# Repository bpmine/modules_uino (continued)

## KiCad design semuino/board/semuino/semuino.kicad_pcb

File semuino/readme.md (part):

# SEMUINO - ECLAIRAGE ARMOIRE A SEMIS

Toutes les plantes ont besoin de lumière.

Les semis ont aussi besoin de lumière.

Pour une croissance optimale, il faut éclairer les semis pendant une certaine durée journalière et avec un spectre de lumière donné (couleurs).

C'est ce que réalise le meuble à semis sur la photo suivante.

## Description de l'éclairage souhaité

Pendant la phase de germinaison et de croissance, il est conseillé d'éclairer avec une teinte composée de 20% de bleu et 80% de rouge.
La lumière doit être répartie de façon homogène pour éviter que les pousses prenent une direction particulière ou/et ne mollissent.

Nous avons choisi une durée d'éclairage de 16 heures par jour.

Pour se rapprocher du cycle naturel, il y'a une montée de la luminosité pendant les 2 premières heures et une descente les 2 dernières heures de la journée.

Pendant la deuxième phase de croissance, la lumière est blanche. Mais les avis divergent. Le meuble permet donc de choisir plusieurs modes d'éclairage.

## Description du meuble

### Composition du meuble

Il est issu de la récupération d'un vieux meuble cassé et dont nous n'avions plus l'usage. 

Le tiroir du bas est utilisé pour mettre des semis.

Le tiroir du milieu est retourné et servira de plafond au premier étage (en bas).

Au dessus du tiroir du milieu pourront être posé des petits plants de plus grande taille. Un tiroir peut également être inséré au dessus pour permettre de poser d'autres semis.

Des bandeaux de LEDs sont collés au dessus et dans le tiroir du milieu. Ils éclairent de façon homogène les semis des deux étages intérieurs.

Il est prévu d'ajouter un étage au dessus du meuble toujours sur le même principe.

### Mode d'emploi

#### Panneau de commande

Le bouton d'alimentation générale 12V permet d'allumer ou d'éteindre le boîtier. Une LED rouge s'allume lorsque celui-ci est en position "marche".

Le bouton d'alimentation auxiliaire 5V permet d'alimenter les LEDs RGB. Une LED bleue s'allume lorsqu'il est dans la position "marche".

Un bouton de sélection permet de modifier le mode de fonctionnement du meuble. Une LED verte permet d'indiquer à l'utilisateur l'état de fonctionnement du meuble.

#### Principe de fonctionnement du sélecteur

Le meuble a trois modes de fonctionnement que l'on peut sélectionner successivement à l'aide du bouton de sélection.

Mode | Nom | Description
--- | --- | ---
0 | OFF | Toutes les LEDs sont éteintes
1 | Auto/Horloge | Les LEDs s'allument entre 6h et 22h selon un mode d'éclairage défini
2 | ON | Les LEDs s'allument

Le mode choisi est sauvegardé dans le boîtier. Lorsqu'on l'éteint et qu'on le rallume, le réglage est retrouvé.

Lorsqu'on change de mode, la LED verte s'allume une première fois puis clignote rapidement autant de fois que le numéro du mode choisi.

La façon dont s'allume les LEDs (étages allumés) est configurable. Ce réglage est aussi mémorisé par le boîtier.

#### Mode de configuration

Pour entrer dans le mode de configuration, il faut appuyer sur le bouton de sélection pendant plus de 4 secondes. 
La LED verte clignote plusieurs fois très rapidement pour indiquer l'entrée dans le menu.
Elle reste ensuite allumée pour indiquer que l'on est dans le mode de configuration

En appuyant sur le bouton de sélection, on peut faire défiler les différents modes d'éclairage. Les LEDs du meuble s'allument en conséquence.
Lorsque le mode d'éclairage souhaité est rencontré, il faut presser pendant environ 4s sur le bouton de sélection jusqu'à ce que la LED verte s'éteigne.

La LED verte clignote ensuite pour rappeller le mode de fonctionnement en cours (voir partie précédente).

#### Récaputulatif de l'état de la LED verte

Etat | Description
Clignote très rapidement au démarrage | Impossible de lire la date et l'heure: Vérifier la pile 3V à l'intérieur. Le meuble est bloqué.
S'allume une fois puis cliqnote n fois rapidement au démarrage | Indique/rapelle le mode de fonctionnement (autant de foir que le numéro de mode)
Eteinte | fonctionnement normal
Cliqnote n fois rapidement après une action | Indique/rapelle le mode de fonctionnement (autant de fois que le numéro de mode)
Clignote toutes les 2s | La terre est sèche: Il faut probablement arroser
Clignote très très rapidement pusieurs fois puis reste allumée | Entrée en mode de configuration de l'éclairage
Allumée fixe | Mode de configuration en cours

#### Usage du bouton de sélection

Action | Description
--- | ---
Appui court | Changer le mode de fonctionnement (OFF / Auto-Horloge / ON)
Appui long | Entrer en mode de configuration

##### En mode configuration

Action | Description
--- | ---
Appui court | Changer le mode d'éclairage des LEDs du meuble
Appui long | Quitter le mode de configuration (et sauver le réglage)
 
#### Description du mode auto

En mode auto, le semuino gère l'éclairage tout seul de la façon suivante:

- De 6h à 7h, la lumière blanche monte toute seule
- de 7h à 12h, la lumière est de type horticole (LEDs RGB et LEDs 12V majoritairement en rouge spécial)
- de 12h à 14h, la lumière est au maxium (LEDs RGB blanches)
- de 14h à 21h, on revient à l'éclairage horticole normal
- de 21h à 22h, la lumière blanche descend toute seule

## Détail technique

### Schéma et conception

[Schéma et PCB de la carte](board/semuino)

Le carte semuino est architecturée autour d'un arduino nano dans sa configuration réduite "standalone".

Elle comporte les éléments suivants:

- Module Nano;
- module RTC;
- module DHT22 pour mesurer l'humidité et la température ambiante;
- trois Sorties de puissance 12V pour alimenter des LEDs horticoles en mode ON/OFF;
- une alimentation 5V pilotable pour alimenter les bandeaux de LEDs LEDs RGB;
- trois sorties pour bandeaux de LEDs RGB;
- trois entrées pour mesure d'humidité du sol;
- un bouton de sélection de mode;
- une entrée/sortie disponible.

Dans cette configuration, le semuino fonctionne de manière autonome. Il se base sur la date et l'heure pour appliquer l'éclairage souhaité.
Il est également possible de prendre en compte la température et l'humidité (en fonction du programme présent dans le nano).
L'utilisateur peut changer le mode à l'aide d'un bouton de sélection.

La version plus élaborée de la carte semuino comporte en plus un ESP01 et une extension pour connecter un petit écran OLED (type SSD1306 128x64).

Dans cette version, l'arduino Nano devient un simple esclave I²C parmi les autres (RTC et écran). C'est le module ESP01 qui gère tout.
Ce dernier peut aussi fonctionner de façon autonome comme pour la configuration précédente.
Mais il peut communiquer en Wifi et disposer de plus de mémoire pour réaliser plus de choses.

L'ensemble logique de la carte est alimenté en 3.3V (Nano, RTC, ESP01, DHT22, ...). Pour le Nano, il est nécessaire d'ajouter une diode pour permettre l'utilisation simultanée de l'alimentation principale avec celle de l'USB.
Le 3.3V de la carte est appliqué à l'entrée d'alimentation 5V du nano. En effet, la broche 3.3V du Nano est une sortie reliée au régulateur intégré de la puce USB. Elle ne sera pas utilisée.

Tous les composants autour du Nano sont alimentés en 3.3V et sont compatibles avec ce niveau de tension. Le fait que le Nano soit alimenté en ~2.6 peut poser un problème de pilotage du signal de data des LEDs RGB pour lesquels la tension requise pour un niveau haut
est de 0.7 Vcc soit 3.5V. En cas de problème, on peut ajouter "en volant" un adaptateur de niveau 3.3V vers 5V qui fera la conversion. Les premiers essais ont validé le schéma initial.

**Attention:** Selon l'alimentation externe utilisée pour obtenir le 5V, il peut être nécessaire d'ajouter un condensateur de filtrage sur le POWER_5V. Cela a été le cas sur notre prototype. Sans ce condensateur, l'alimentation 5V n'était pas correctement filtrée et le bandeau RGB ne fonctionnait pas. 
Au mieux il clignotait, au pire il affichait des couleurs aléatoires.

### Composants

#### Externes

Nom | Description
--- | --- 
WS2812B 5m 300 LEDs | Bandeau RGB avec 300 LEDs / 5M / 18W
 ? | Capteur d'humidité capatitif
SSD1306 | Ecran OLEB 128x64

#### Sur la carte (principaux)

Nom | Description
--- | --- 
DHT22 | Capteur de température et d'humidité ambiante
Nano | Module Arduino Nano
ESP01 | Module ESP01 (pour connectivité wifi et pilotage de LCD)
RTC | Module RTC avec pile 3V
... | ...

A compléter...

### Les logiciels

Il y'a plusieurs types de logiciels différents pour l'arduino Nano:

Nom | Description | Lien
--- | --- | ---
semuino_test|Pour tester la carte semuino | 
semuino|Le programme standalone standard pour le Nano |
semuino_nano_slave|Le programme esclave I²C pour le nano |
semuino_nano_master_test|Un programme de test pour remplacer un maître I²C avec un Nano |

Le Nano est quasiment plein niveau RAM. Il n'est pas possible de gérer les trois RGB en même temps. Le RGB3 a pour l'instant été retiré.
Au niveau temps de cycle, il n'est pas possible d'utiliser le DHT22 en même temps que le bus I²C.

Pour l'ESP01, il n'y a qu'un seul programme:
Nom | Description | Lien
--- | --- | ---
semuino_esp01_master|Programme SEMUINO complet pour ESP01 | 

## Protocole d'échange I²C (Esclave Nano)

L'I²C permet à l'ESP01 d'accéder à l'écran, au RTC et au Nano. Cette partie décrit la gestion de l'esclave par le programme du Nano.

### Description des échanges I²C

Adresse de l'esclave: 0xA

Pour écrire une valeur, on envoie le numéro de registre (1 octet) puis la donnée à écrire.

Registre | Nom | R/W  | Taille | Description
--- | --- | --- | --- | ---
1 | Commandes | Ecriture | 1 octet | Contient les commandes pour agir sur les bandeaux de LEDs
2 | Level | Ecriture | 1 octet | Défini le niveau d'éclairage des LEDs RGB (entre 1 et 255)
3 | Modes RGB A | Ecriture | 1 octet | Contient les modes des bandeaux RGB 1 (4 bits de poids faible) et RGB 2 (4 bits de poids fort)
4 | Modes RGB B | Ecriture | 1 octet | Les 4 bits de poids faible correspondent au mode du bandeau RGB 3
5 | WRITE EEPROM | Ecriture | 2 octets | Le premier octet contient l'adresse EEPROM où écrire et le second contient la donnée à écrire
6 | Voyants | Ecriture | 1 octet | Etat des voyants (bit 0: LED verte)

Pour lire une valeur, on envoie le numéro de registre (1 octet) puis on demande la lecture des données.

Registre | Nom | R/W  | Taille | Description
--- | --- | --- | --- | ---
10 | Inputs | Lecture | 1 octet | Retourne l'état des entrées (bit 0: bouton de select)
11 | TEMP | Lecture | 1 octet | Retourne la température ambiante (en °C)
12 | HUM | Lecture | 1 octet | Retourne le taux d'humidité ambiante (en %)
13 | H1 | Lecture | 1 octet | Retourne la valeur du capteur d'humidité du sol n° 1 (0..255)
14 | H2 | Lecture | 1 octet | Retourne la valeur du capteur d'humidité du sol n° 2 (0..255)
15 | H3 | Lecture | 1 octet | Retourne la valeur du capteur d'humidité du sol n° 3 (0..255)
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
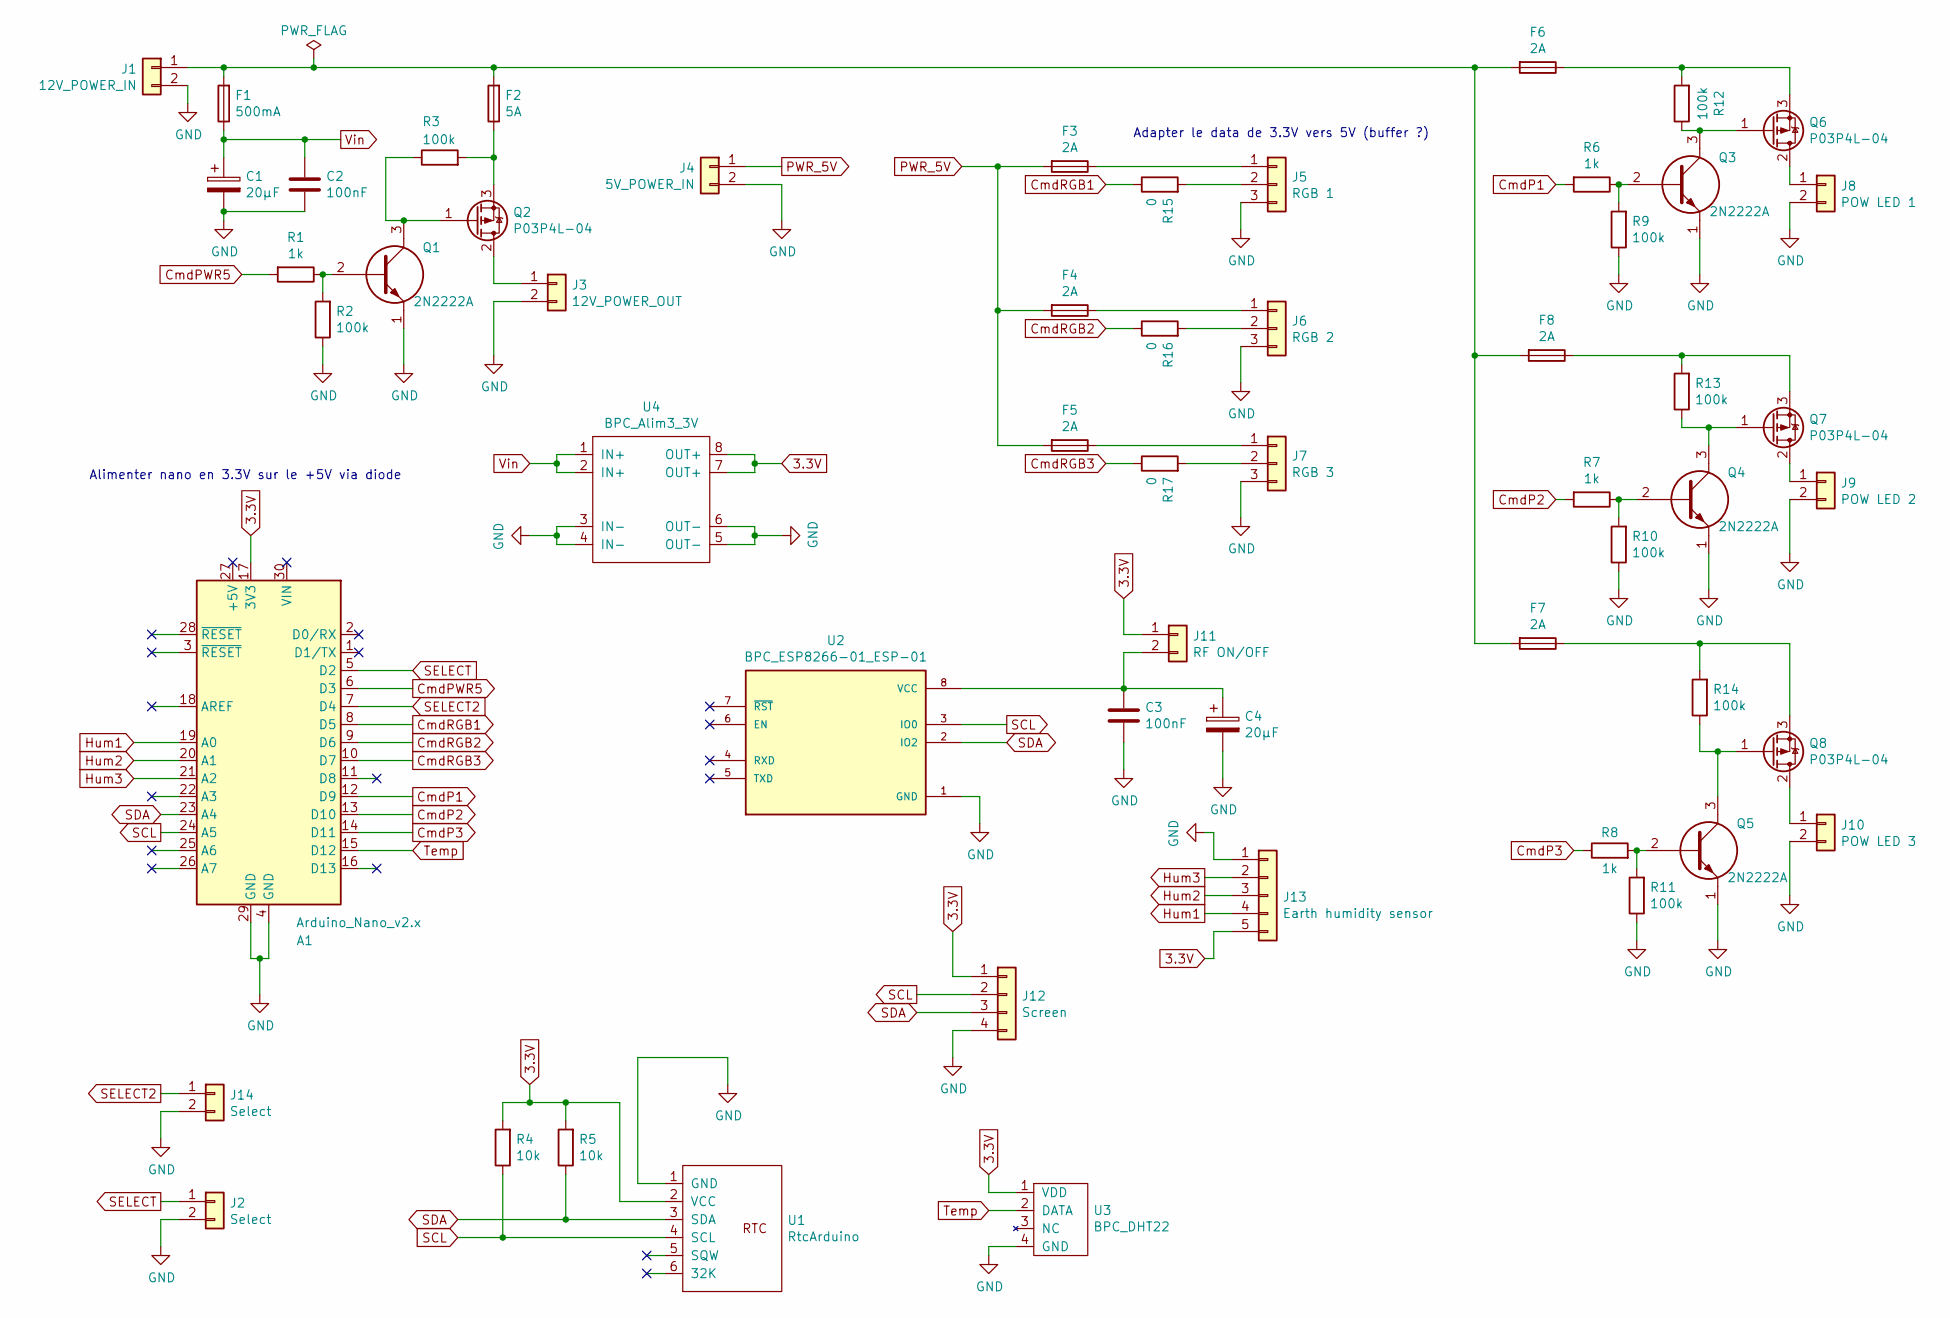
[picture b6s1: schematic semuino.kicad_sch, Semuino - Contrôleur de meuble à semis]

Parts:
A1: Arduino_Nano_v2.x; BPC_Arduino_Nano
C1, C4: 20µF; CP_Radial_D8.0mm_P3.80mm
C2, C3: 100nF; C_Disc_D7.0mm_W2.5mm_P5.00mm
F1: 500mA; Fuseholder_TR5_Littelfuse_No560_No460
F2: 5A; Fuseholder_Clip-5x20mm_Littelfuse_520_Inline_P20.50x5.80mm_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
F3, F4, F5, F6, F7, F8: 2A; Fuseholder_TR5_Littelfuse_No560_No460
J1: 12V_POWER_IN; TerminalBlock_Phoenix_MKDS-1,5-2_1x02_P5.00mm_Horizontal
J2, J14: Select; PinHeader_1x02_P2.54mm_Vertical
J3: 12V_POWER_OUT; TerminalBlock_Phoenix_MKDS-1,5-2_1x02_P5.00mm_Horizontal
J4: 5V_POWER_IN; TerminalBlock_Phoenix_MPT-0,5-2-2.54_1x02_P2.54mm_Horizontal
J5: RGB 1; TerminalBlock_Phoenix_MPT-0,5-3-2.54_1x03_P2.54mm_Horizontal
J6: RGB 2; TerminalBlock_Phoenix_MPT-0,5-3-2.54_1x03_P2.54mm_Horizontal
J7: RGB 3; TerminalBlock_Phoenix_MPT-0,5-3-2.54_1x03_P2.54mm_Horizontal
J8: POW LED 1; TerminalBlock_Phoenix_MKDS-1,5-2_1x02_P5.00mm_Horizontal
J9: POW LED 2; TerminalBlock_Phoenix_MKDS-1,5-2_1x02_P5.00mm_Horizontal
J10: POW LED 3; TerminalBlock_Phoenix_MKDS-1,5-2_1x02_P5.00mm_Horizontal
J11: RF ON/OFF; PinHeader_1x02_P2.54mm_Vertical
J12: Screen; JST_XH_B4B-XH-A_1x04_P2.50mm_Vertical
J13: Earth humidity sensor; TerminalBlock_Phoenix_MPT-0,5-5-2.54_1x05_P2.54mm_Horizontal
Q1, Q3, Q4, Q5: 2N2222A; TO-92; Manufacturer_Part_Number 2N2222A; Mouser Part Number 494-2N2222A
Q2, Q6, Q7, Q8: P03P4L-04; TO-220-3_Vertical
R1, R6, R7, R8: 1k; R_Axial_DIN0309_L9.0mm_D3.2mm_P2.54mm_Vertical
R2, R3, R9, R10, R11, R12, R13, R14: 100k; R_Axial_DIN0309_L9.0mm_D3.2mm_P2.54mm_Vertical
R4, R5: 10k; R_Axial_DIN0309_L9.0mm_D3.2mm_P12.70mm_Horizontal
R15, R16, R17: 0; R_Axial_DIN0309_L9.0mm_D3.2mm_P2.54mm_Vertical
U1: RtcArduino; BPC_RtcArduino
U2: BPC_ESP8266-01_ESP-01; BPC_XCVR_ESP8266-01_ESP-01; PARTREV V1.2
U3: BPC_DHT22
U4: BPC_Alim3_3V

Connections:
3.3V: A1.17 (3V3), J11.1, J12.1, J13.5, R4.2, R5.2, U1.2 (VCC), U3.1 (VDD), U4.7 (OUT+), U4.8 (OUT+)
CmdP1: A1.12 (D9), R6.2
CmdP2: A1.13 (D10), R7.2
CmdP3: A1.14 (D11), R8.1
CmdPWR5: A1.6 (D3), R1.2
CmdRGB1: A1.8 (D5), R15.1
CmdRGB2: A1.9 (D6), R16.1
CmdRGB3: A1.10 (D7), R17.1
GND: A1.4 (GND), A1.29 (GND), C1.2, C2.2, C3.2, C4.2, J1.2, J2.2, J3.2, J4.2, J5.3, J6.3, J7.3, J8.2, J9.2, J10.2, J12.4, J13.1, J14.2, Q1.1, Q3.1, Q4.1, Q5.1, R2.1, R9.1, R10.1, R11.1, U1.1 (GND), U2.1 (GND), U3.4 (GND), U4.3 (IN-), U4.4 (IN-), U4.5 (OUT-), U4.6 (OUT-)
Hum1: A1.19 (A0), J13.4
Hum2: A1.20 (A1), J13.3
Hum3: A1.21 (A2), J13.2
unnamed: F1.2, F2.2, F6.2, F7.2, F8.2, J1.1
unnamed: J3.1, Q2.2 (D)
unnamed: F3.1, J5.1
unnamed: J5.2, R15.2
unnamed: F4.1, J6.1
unnamed: J6.2, R16.2
unnamed: F5.1, J7.1
unnamed: J7.2, R17.2
unnamed: J8.1, Q6.2 (D)
unnamed: J9.1, Q7.2 (D)
unnamed: J10.1, Q8.2 (D)
unnamed: C3.1, C4.1, J11.2, U2.8 (VCC)
unnamed: Q1.2, R1.1, R2.2
unnamed: Q1.3, Q2.1 (G), R3.1
unnamed: F2.1, Q2.3 (S), R3.2
unnamed: Q3.2, R6.1, R9.2
unnamed: Q4.2, R7.1, R10.2
unnamed: Q5.2, R8.2, R11.2
unnamed: Q3.3, Q6.1 (G), R12.1
unnamed: F6.1, Q6.3 (S), R12.2
unnamed: Q4.3, Q7.1 (G), R13.1
unnamed: F8.1, Q7.3 (S), R13.2
unnamed: Q5.3, Q8.1 (G), R14.1
unnamed: F7.1, Q8.3 (S), R14.2
PWR_5V: F3.2, F4.2, F5.2, J4.1
SCL: A1.24 (A5), J12.2, R4.1, U1.4 (SCL), U2.3 (IO0)
SDA: A1.23 (A4), J12.3, R5.1, U1.3 (SDA), U2.2 (IO2)
SELECT: A1.5 (D2), J2.1
SELECT2: A1.7 (D4), J14.1
Temp: A1.15 (D12), U3.2 (DATA)
Vin: C1.1, C2.1, F1.1, U4.1 (IN+), U4.2 (IN+)

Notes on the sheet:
Alimenter nano en 3.3V sur le +5V via diode
Adapter le data de 3.3V vers 5V (buffer ?)

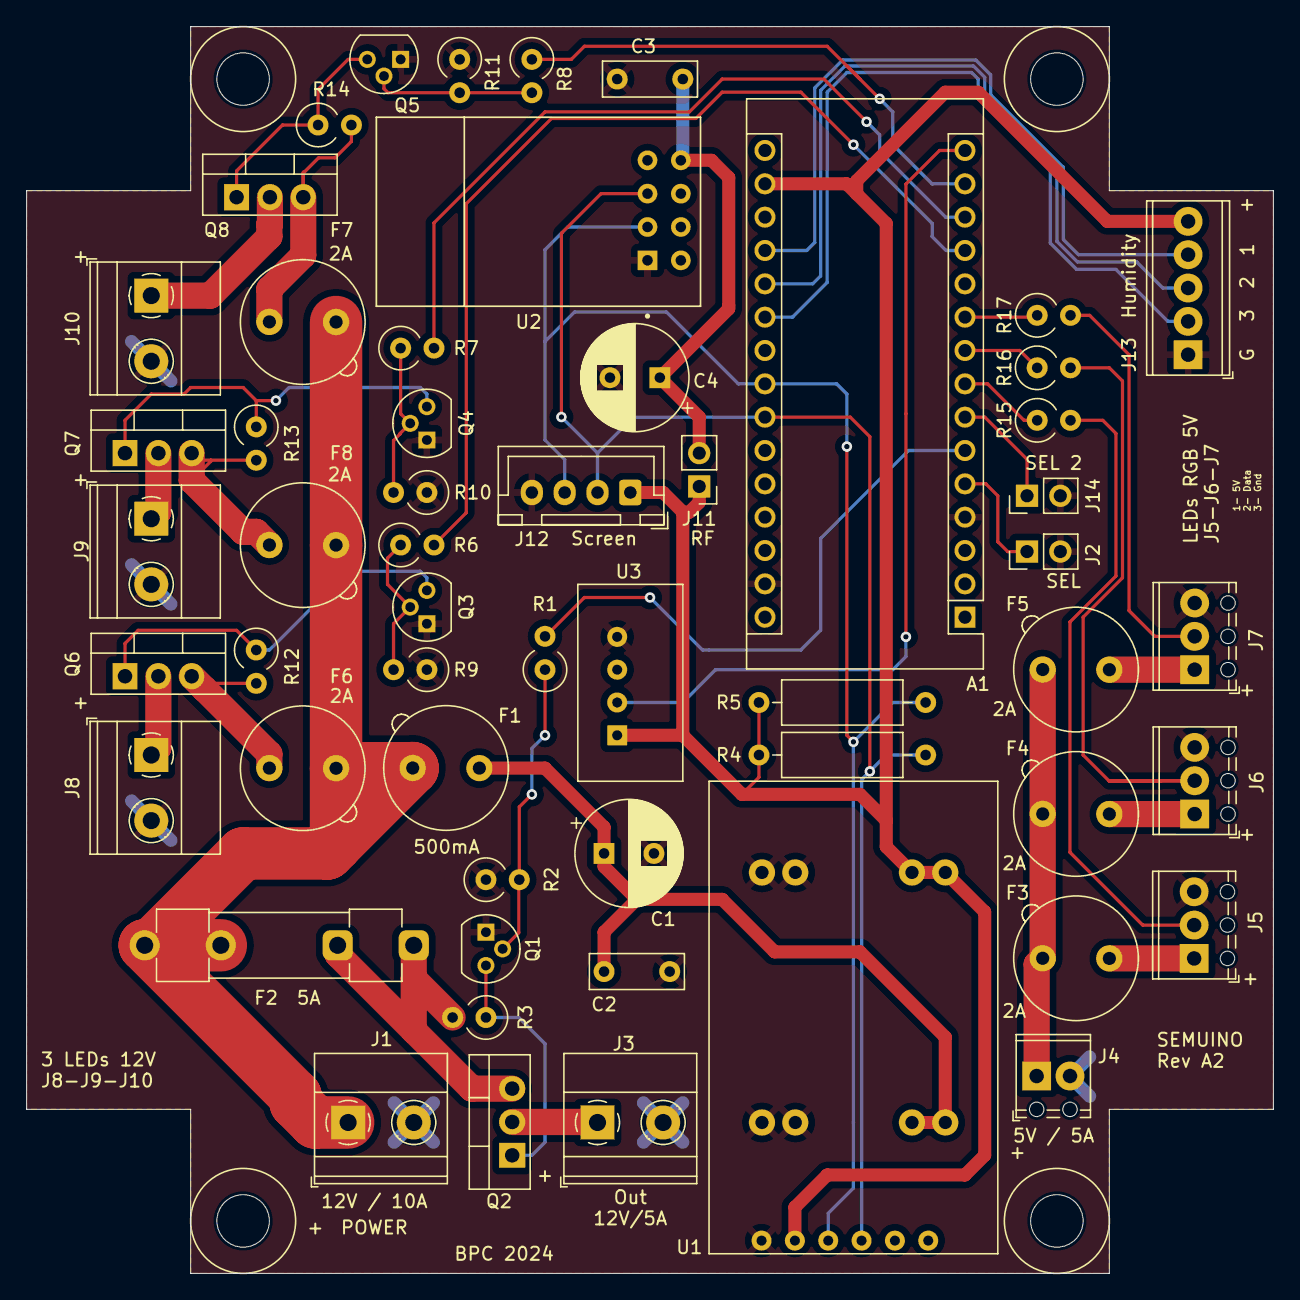
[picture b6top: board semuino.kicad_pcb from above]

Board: 2 copper layers, 95.0 x 95.0 mm, 56 parts (1 on the bottom side), 43 nets.

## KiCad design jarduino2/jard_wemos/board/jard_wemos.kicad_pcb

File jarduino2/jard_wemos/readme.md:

# Modules de commande des pompes en Wifi (jard_wemos)

Cette partie comporte la description de modules Wifi permettant de commander les pompes de transfert entre cuves.

Plusieurs cuves contiennent de l'eau de récupération des pluies.

Les cuves principales sont toujours en exédant d'eau, alors que les cuves proches des coins jardin sont en déficit d'eau.

Le rôle de ce système est de permettre un transfert d'eau automatique ou piloté à distance.

## Schéma d'ensemble des cuves

## Architecture du système

## Description des composants du système
### Module de pompage

Le module de pompage comporte:
- 1 alimentation 12V;
- 1 sortie pompe de 12V/5A;
- 3 entrées de type interrupteur (actif à l'état bas) pour la détection du niveau de cuve.

### Module d'affichage

Le module d'affichage comporte un écran, OLED.

Il permet de visualiser l'état des cuves et l'activité de pompage en temps réel.

### Serveur de contrôle

Le serveur comporte un broker MQTT pour centraliser les connexions des différents modules du système.

Un serveur reddis stocke tous les états, les réglages et les commandes des différentes applications.

Les applications sont les suivantes:
- Interraction avec les modules de pompage
- Publication des états sur les écrans
- Webservice pour exposer les services à des clients
- Automatisme de contrôle
- Logger

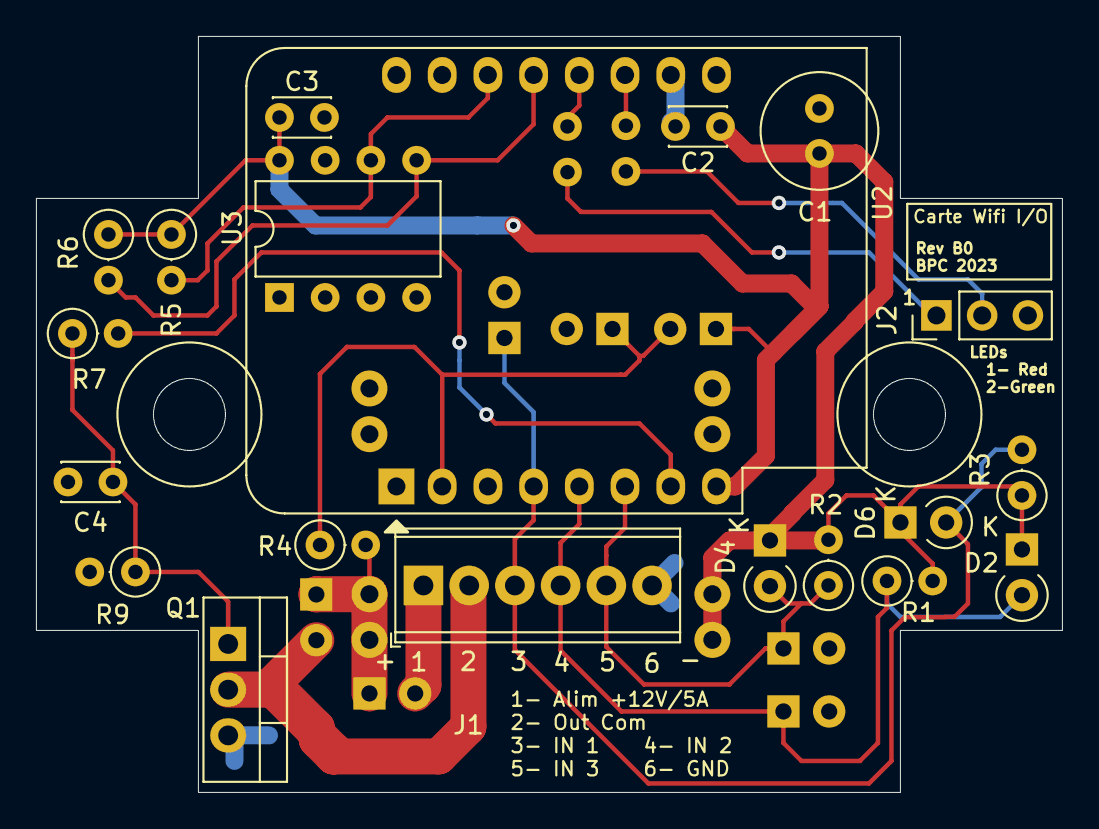
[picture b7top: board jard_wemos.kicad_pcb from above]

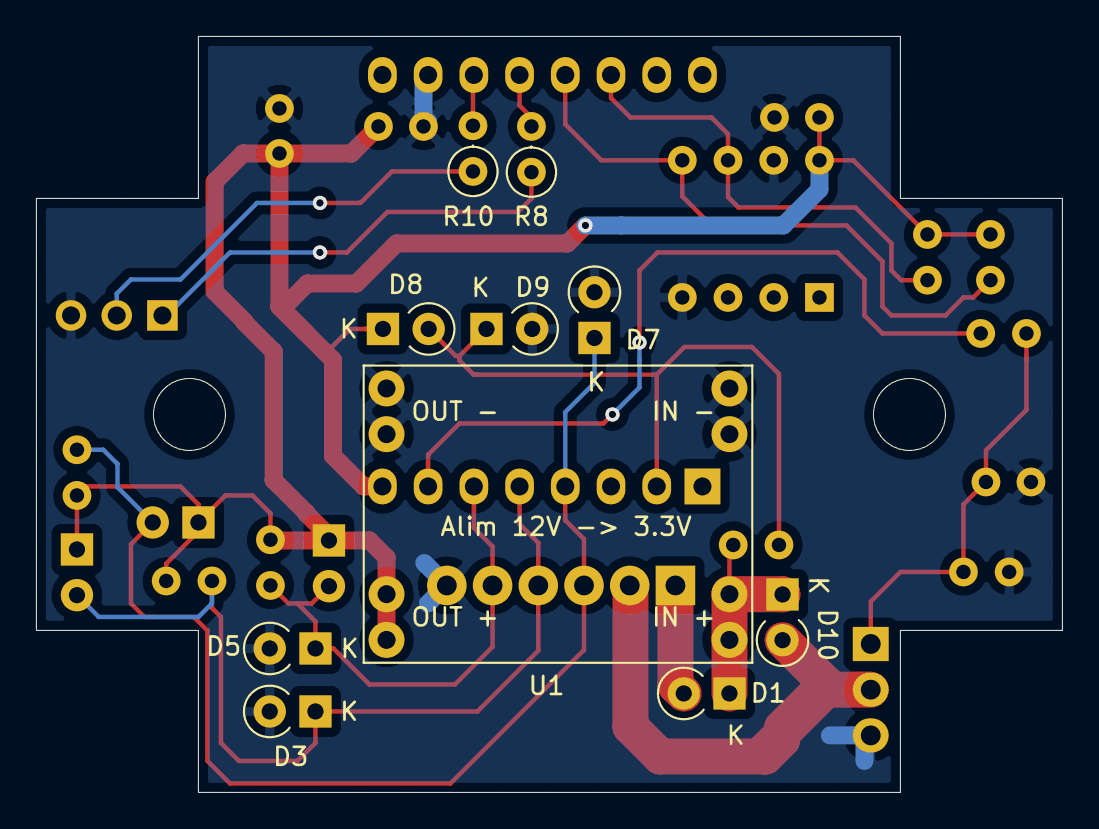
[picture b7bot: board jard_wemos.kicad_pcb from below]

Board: 2 copper layers, 57.0 x 42.0 mm, 30 parts (10 on the bottom side), 17 nets.

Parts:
C1: 20µF; C_Radial_D6.3mm_H7.0mm_P2.50mm
C2, C3, C4: 100n; C_Disc_D3.0mm_W2.0mm_P2.50mm
D1, D2, D3, D4, D5, D6, D7, D8, D9, D10: D; D_A-405_P2.54mm_Vertical_KathodeUp
J1: Conn_01x05; TerminalBlock_Phoenix_MPT-0,5-6-2.54_1x06_P2.54mm_Horizontal
J2: LEDs; PinHeader_1x03_P2.54mm_Vertical
Q1: BPC_IPP034N03L; TO-220-3_Vertical
R1, R2, R3, R9: 100k; R_Axial_DIN0207_L6.3mm_D2.5mm_P2.54mm_Vertical
R4: 1,2M; R_Axial_DIN0207_L6.3mm_D2.5mm_P2.54mm_Vertical
R5, R6: 10k; R_Axial_DIN0207_L6.3mm_D2.5mm_P2.54mm_Vertical
R7: 50; R_Axial_DIN0207_L6.3mm_D2.5mm_P2.54mm_Vertical
R8, R10: 100; R_Axial_DIN0207_L6.3mm_D2.5mm_P2.54mm_Vertical
U1: BPC_Alim3_3V
U2: WeMos_D1_mini; WEMOS_D1_mini_light
U3: 24LC01; DIP-8_W7.62mm

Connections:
+3V3: C1.1, C2.1, C3.2, D2.1, D4.1, D6.1, D8.1, R1.2, R2.2, R3.1, R5.1, R6.1, U1.7, U1.8, U2.8, U3.8
+12V: D1.1, D10.1, R4.2, U1.1, U1.2
CMD_OUT_12V: R7.2, U2.7
GND: C1.2, C2.2, C3.1, C4.2, D3.2, D5.2, D7.2, D9.2, J1.6, J2.3, Q1.3, R9.2, U1.3, U1.4, U1.5, U1.6, U2.10, U3.4, U3.7
IN_1: D6.2, D7.1, J1.3, R3.2, U2.4
IN_2: D2.2, D3.1, J1.4, R1.1, U2.5
IN_3: D4.2, D5.1, J1.5, R2.1, U2.6
LED_ROUGE: R8.2, U2.12
LED_VERTE: R10.2, U2.11
unnamed: C4.1, Q1.1, R7.1, R9.1
unnamed: D1.2, J1.1
unnamed: J2.1, R8.1
unnamed: J2.2, R10.1
unnamed: R5.2, U2.14, U3.6
unnamed: R6.2, U2.13, U3.5
OUT_12V_COM: D10.2, J1.2, Q1.2
POW_MES: D8.2, D9.1, R4.1, U2.2

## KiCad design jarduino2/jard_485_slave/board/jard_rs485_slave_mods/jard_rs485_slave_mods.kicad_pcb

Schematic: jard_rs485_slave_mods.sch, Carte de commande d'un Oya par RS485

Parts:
A1: Arduino_Nano_v2.x; BPC_Arduino_Nano
C1: 10n; C_Disc_D5.0mm_W2.5mm_P2.50mm
C2: 10µF; CP_Radial_D8.0mm_P2.50mm
C3, C4: 100n; C_Disc_D5.0mm_W2.5mm_P2.50mm
D1: D; D_A-405_P12.70mm_Horizontal
D2, D3, D4: D; D_A-405_P2.54mm_Vertical_AnodeUp
J1: NETWORK IN; TerminalBlock_Phoenix_MPT-0,5-4-2.54_1x04_P2.54mm_Horizontal
J2: NETWORK OUT; TerminalBlock_Phoenix_MPT-0,5-4-2.54_1x04_P2.54mm_Horizontal
J3, J4: LED; PinHeader_1x02_P2.54mm_Vertical
J5: Debit; TerminalBlock_Phoenix_MPT-0,5-3-2.54_1x03_P2.54mm_Horizontal
J6: Niveau; TerminalBlock_Phoenix_MPT-0,5-3-2.54_1x03_P2.54mm_Horizontal
J7: Electrovanne 12V; TerminalBlock_Phoenix_MPT-0,5-2-2.54_1x02_P2.54mm_Horizontal
Q1: BPC_2N2222A; TO-18-3; Manufacturer_Part_Number 2N2222A; Mouser Part Number 494-2N2222A
Q2: P03P4L-04; TO-220-3_Vertical
R1, R2: 150; R_Axial_DIN0309_L9.0mm_D3.2mm_P2.54mm_Vertical
R3, R4, R6, R7, R8, R9, R10: 100k; R_Axial_DIN0309_L9.0mm_D3.2mm_P2.54mm_Vertical
R5: 100; R_Axial_DIN0309_L9.0mm_D3.2mm_P2.54mm_Vertical
R11: 40k; R_Axial_DIN0309_L9.0mm_D3.2mm_P2.54mm_Vertical
R12: 30mR; R_Axial_DIN0309_L9.0mm_D3.2mm_P2.54mm_Vertical
R13: 10k; R_Axial_DIN0309_L9.0mm_D3.2mm_P2.54mm_Vertical
R14: 1k; R_Axial_DIN0309_L9.0mm_D3.2mm_P2.54mm_Vertical
R15: 32k; R_Axial_DIN0309_L9.0mm_D3.2mm_P2.54mm_Vertical
U1: BPC_Mod485
U2: BPC_DHT22
U3: LM358; DIP-8_W7.62mm_Socket_LongPads

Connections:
CMD_EV: A1.10 (D7), R5.2
FLOW_IN: A1.7 (D4), J5.2, R4.2
GND: A1.4 (GND), A1.29 (GND), C1.1, C2.2, C3.1, C4.1, D4.2 (A), J1.4, J2.4, J3.2, J4.2, J5.3, J6.3, Q1.1, R3.2, R6.2, R11.2, R12.2, R14.2, U1.4, U2.4, U3.4, U3.5, U3.6
IN_LVL_HIGH: A1.6 (D3), J6.2, R8.2
IN_LVL_LOW: A1.5 (D2), J6.1, R7.2
LED1: A1.11 (D8), R1.1
LED2: A1.12 (D9), R2.1
MES_I: A1.19 (A0), R15.1, U3.1
MES_V: A1.20 (A1), D3.2 (A), D4.1 (K), R10.2, R11.1
unnamed: A1.30 (VIN), C1.2, C2.1, D1.1 (K), Q2.3, R9.1
unnamed: C3.2, R13.1, U3.3
unnamed: D1.2 (A), J1.1, J2.1
unnamed: D2.1 (K), J7.2, Q2.2, R10.1
unnamed: D2.2 (A), J7.1, R12.1, R13.2
unnamed: J1.2, J2.2, U1.3
unnamed: J1.3, J2.3, U1.2
unnamed: J3.1, R1.2
unnamed: J4.1, R2.2
unnamed: Q1.2, R5.1, R6.1
unnamed: Q1.3, Q2.1, R9.2
unnamed: R14.1, R15.2, U3.2
RX: A1.2 (D0/RX), U1.8
TEMP: A1.13 (D10), U2.2
TX: A1.1 (D1/TX), U1.5
TXEN: A1.9 (D6), R3.1, U1.6, U1.7
Vcc: A1.27 (+5V), C4.2, D3.1 (K), J5.1, R4.1, R7.1, R8.1, U1.1, U2.1, U3.8

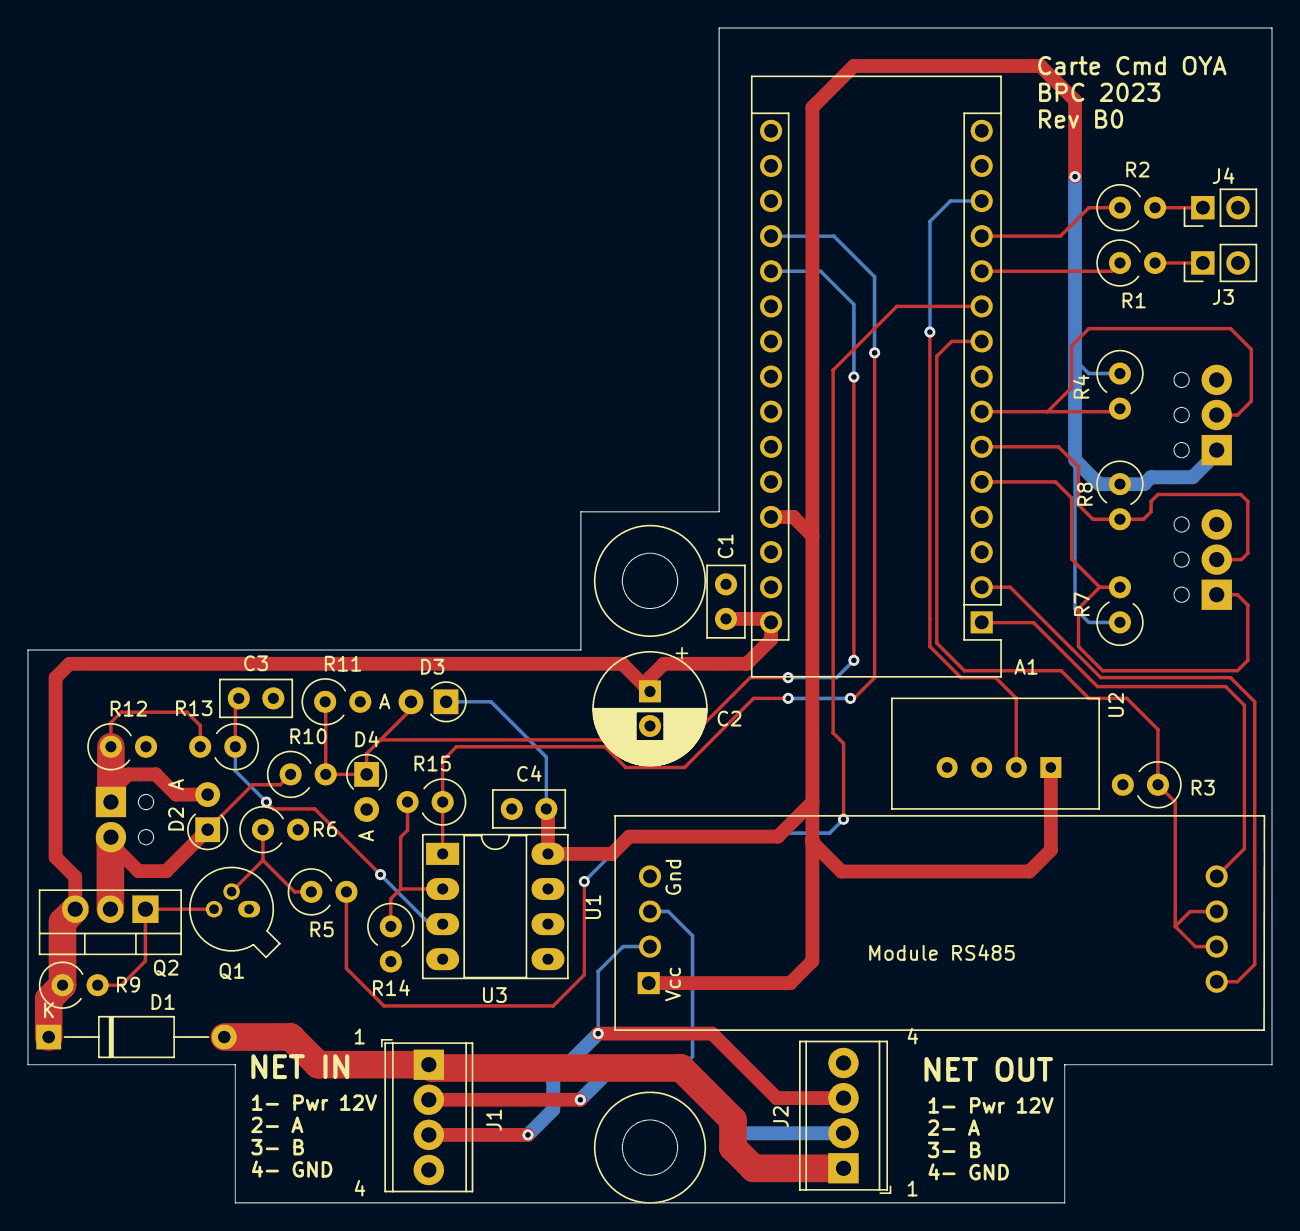
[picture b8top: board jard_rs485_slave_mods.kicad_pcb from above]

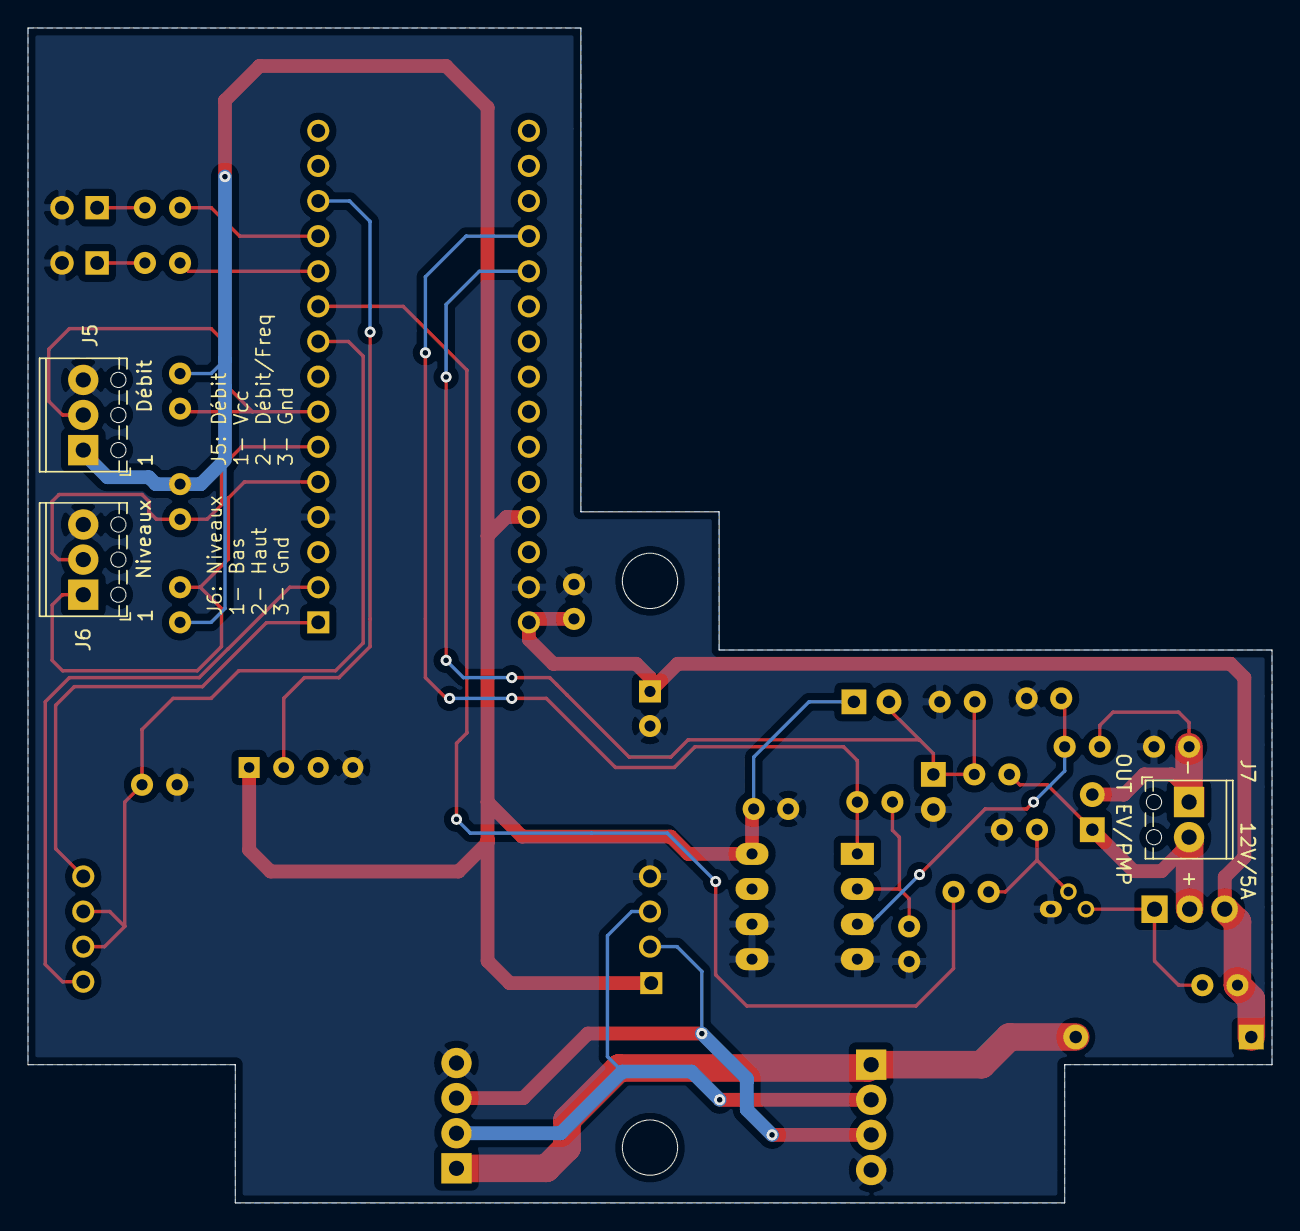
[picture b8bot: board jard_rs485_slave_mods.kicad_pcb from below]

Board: 2 copper layers, 90.0 x 85.0 mm, 36 parts (3 on the bottom side), 26 nets.

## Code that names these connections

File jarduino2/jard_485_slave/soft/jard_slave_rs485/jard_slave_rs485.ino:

/**
 * @file jard_slave_rs485.ino
 * @brief Programme d'un esclave RS485 de gestion d'un OYA (ou d'une pompe)
*/
#include "client.h"
#include "globals.h"
#include "eep_slave.hpp" .
#include "slavearduino.hpp"
#include "timer.h"
#include "pins.h"

#include <avr/wdt.h>

//#define DEBUG_TRACE
//#define INIT_AND_SET_ADDR
//#define ENABLE_WDG

//#define NO_DHT
//#define NO_FLOW
//#define NO_ANALOG

#ifdef INIT_AND_SET_ADDR
  //#define INIT_ADDR 2
  #define INIT_ADDR 'Z'
  #define DEBUG_TRACE
#endif

bool g_on=false;
bool g_cpt_low=false;
bool g_cpt_high=false;
unsigned char g_mes_cv;
bool g_reset_because_of_wdg=false;

int g_flow_mLpMin=-1;
char g_temp_dg=0;
char g_hum_pc=0;
unsigned short g_total_s=0;
unsigned short g_errors=0;

#ifndef NO_DHT
  #include <DHT.h>
  DHT dht(PIN_DHT22, DHT22);
#endif

#ifndef NO_FLOW
  #include "flow.hpp" 
#endif

#ifndef NO_ANALOG
  #include "analog.hpp" 
  Analog anMesV;
#endif

Timer tmrSec(1000,false);
Timer tmr500ms(500,false);
Timer tmr200ms(200,false);

bool flg200ms=false;
bool flg500ms=false;

unsigned char getSlaveAddress(void)
{
  unsigned char addr=0;
  if (digitalRead(PIN_ADDR_A1)==LOW)
   addr|=0x01;
  if (digitalRead(PIN_ADDR_A2)==LOW)
   addr|=0x02;
  if (digitalRead(PIN_ADDR_A3)==LOW)
   addr|=0x04;
  if (digitalRead(PIN_ADDR_A4)==LOW)
   addr|=0x08;

  return addr;
}

void setup() 
{
  #ifdef ENABLE_WDG 
    unsigned char mcusr=MCUSR;
    if (MCUSR & (1 << WDRF))
      g_reset_because_of_wdg=true;
      
    MCUSR = 0;
  #endif

  wdt_disable();
  
  pinMode(PIN_CMD_EV,OUTPUT);
  digitalWrite(PIN_CMD_EV,LOW);
  pinMode(PIN_LED1,OUTPUT);
  digitalWrite(PIN_LED1,LOW);

  /// @warning Les deux entrées LOW/HIGH n'ont pas de pullup externe sur les cartes Rev Ex. Donc il les faut en interne
  pinMode(PIN_CPT_LVL_LOW,INPUT_PULLUP);
  pinMode(PIN_CPT_LVL_HIGH,INPUT_PULLUP);
  pinMode(PIN_CPT_FLOW,INPUT);

  pinMode(PIN_MES_V,INPUT);

  pinMode(PIN_ADDR_A1,INPUT_PULLUP);
  pinMode(PIN_ADDR_A2,INPUT_PULLUP);
  pinMode(PIN_ADDR_A3,INPUT_PULLUP);
  pinMode(PIN_ADDR_A4,INPUT_PULLUP);

  pinMode(PIN_TX_EN,OUTPUT);
  digitalWrite(PIN_TX_EN,LOW);

  pinMode(PIN_DGB_SYNC,OUTPUT);
  digitalWrite(PIN_DGB_SYNC,LOW);

  pinMode(PIN_DGB_CMD,OUTPUT);
  digitalWrite(PIN_DGB_CMD,LOW);

  pinMode(LED_BUILTIN,OUTPUT);
  digitalWrite(LED_BUILTIN,LOW);

  /// @remark On clignote 5 fois rapidement au boot
  for (int i=0;i<5;i++)
  {
    delay(100);
    digitalWrite(LED_BUILTIN,HIGH);
    delay(100);
    digitalWrite(LED_BUILTIN,LOW);
  }  
  digitalWrite(LED_BUILTIN,LOW);
  tmrSec.start();

  g_cpt_low=false;
  g_cpt_high=false;
  g_on=false;
  g_flow_mLpMin=-1;
  
  g_total_s=0;
  g_errors=0;

  #ifndef NO_DHT
    dht.begin();
  #endif
  #ifndef NO_FLOW
    Flow.begin(PIN_CPT_FLOW);
  #endif

  #ifdef INIT_AND_SET_ADDR
    unsigned char tmp;
    Eep::readID(&tmp); /// Pour etre sur EEP bien init
    Eep::writeID(INIT_ADDR);
  #endif

  unsigned char addr=getSlaveAddress();
  unsigned char laddr=0xFF;
  do
  {
    delay(5);
    laddr=addr;
    addr=getSlaveAddress();    
  } while (addr!=laddr);
  
  if (addr==0)
  {
    /// Si le selecteur d'adresse est sur '0' (ou non monte), on lit l'adresse en EEPROM
    Eep::readID(&addr);
  }

  if (addr>=15)
    addr='Z';

  Slave.begin(addr);

  g_total_s=Eep::readTotalTimeCtr();
  g_errors=Eep::readTotalErrCtr();

  #ifdef DEBUG_TRACE
    Serial.print("Boot @");
    if (addr=='Z')
      Serial.println("Z");
    else
      Serial.println(addr);

    for (int i=0;i<500;i++)
    {
      delay(1);
      yield();
    }
    
    Serial.print("Total: ");
    Serial.print(g_total_s);
    Serial.println(" s");
    for (int i=0;i<500;i++)
    {
      delay(1);
      yield();
    }

    Serial.print("Errs: ");
    Serial.println(g_errors);
    for (int i=0;i<500;i++)
    {
      delay(1);
      yield();
    }
  #endif

  #ifdef INIT_AND_SET_ADDR
    Serial.print("FORCE ADDRESS INIT: ");
    Serial.println(INIT_ADDR);
    for (int i=0;i<500;i++)
    {
      delay(1);
      yield();
    }
  #endif 

  /// @remark Attendre au moins 1s apres le clignotement de boot
  while (tmrSec.tick()==false);
  
  /// @remark Si adresse Z, on bloque tout en clignotant lentement (1s)
  if (addr=='Z')
  {
    bool blk=false;
    while (1)
    {
      if (tmrSec.tick()==true)
        blk=!blk;
        
      digitalWrite(PIN_LED1,blk?HIGH:LOW);
      digitalWrite(LED_BUILTIN,blk?HIGH:LOW);
      
      yield();
    }
  }

  #ifdef ENABLE_WDG
    cli();
    wdt_reset();
    wdt_enable(WDTO_500MS);
    sei();

    if (g_reset_because_of_wdg==true)
    {
      g_errors++;
      Eep::writeTotalErrCtr(g_errors);      
    }
  #endif

  flg200ms=false;
  flg500ms=false;

  tmrSec.start();
  tmr500ms.start();
  tmr200ms.start();  
}

void serialEvent()
{
  Slave.onSerialEvent();
}

void loop() 
{
  #ifdef INIT_AND_SET_ADDR
    /// @remark S'allume brievement toutes les secondes si soft d'initialisation
    digitalWrite(PIN_LED1,LOW);
    digitalWrite(LED_BUILTIN,LOW);
    delay(200);
    digitalWrite(PIN_LED1,HIGH);
    digitalWrite(LED_BUILTIN,HIGH);
    delay(1000);
    return;
  #endif

  /// @remark Au repos, le niveau doit être high (capteur non branché)
  #ifndef NO_FLOW
    g_flow_mLpMin=Flow.getFlow();
  #endif
  g_cpt_low=digitalRead(PIN_CPT_LVL_LOW)==HIGH?true:false;
  g_cpt_high=digitalRead(PIN_CPT_LVL_HIGH)==HIGH?true:false;
  #ifndef NO_ANALOG
    anMesV.latch((unsigned short)analogRead(PIN_MES_V));  
  #endif  

  /// @remark Gestion de la comm de l'esclave. true a chaque fin de cycle / trame "S"
  if (Slave.loop()==true)
  {
     digitalWrite(PIN_DGB_SYNC,HIGH);

     #ifndef NO_DHT
  	   float tmp = dht.readHumidity();
  	   if ((isnan(tmp)) || (tmp<0) || (tmp>100) )
  	     g_hum_pc=-1;
  	   else
  	     g_hum_pc=(char)trunc(tmp);
  
  	   tmp = dht.readTemperature();
  	   if ( (isnan(tmp)) || (tmp<-50) || (tmp>100) )
  	     g_temp_dg=-127;
  	   else
  	     g_temp_dg=(char)trunc(tmp);
     #endif

     #ifndef NO_ANALOG
  	   unsigned long v=(unsigned long)anMesV.get();    
       v=v*120/669;
       if (v>255)
        v=255;
       g_mes_cv=(unsigned char)v;
     #endif
     
     digitalWrite(PIN_DGB_SYNC,LOW);
  }  
 
  if (!Slave.isAlive())
  {
	  g_on=false;
  }
  else
  {
	  g_on=Slave.isCmd();
  }

  #ifndef NO_FLOW
    Flow.tick();
  #endif
  
  if (tmrSec.tick()==true)
  {    
    if (g_on==true)
    {
      g_total_s++;
      Eep::writeTotalTimeCtr(g_total_s);
    }
  }
  
  if (tmr200ms.tick()==true)
  {
    flg200ms=!flg200ms;
  }

  if (tmr500ms.tick()==true)
  {
    flg500ms=!flg500ms;
  }

  digitalWrite(PIN_CMD_EV,g_on==true?HIGH:LOW);

  /// @remark LED clignote tres vite si ON, moins vite si pas de Synchro et fixe si synchro ok
  if (Slave.isAlive()==true)
  {
    if (g_on==true)
    {
      digitalWrite(LED_BUILTIN,flg200ms?HIGH:LOW);
      digitalWrite(PIN_LED1,flg200ms?HIGH:LOW);
    }
    else if (Slave.isSyncOk()==false)
    {
      digitalWrite(LED_BUILTIN,flg500ms?HIGH:LOW);
      digitalWrite(PIN_LED1,flg500ms?HIGH:LOW);
    }
    else
    {
      digitalWrite(LED_BUILTIN,HIGH);
      digitalWrite(PIN_LED1,HIGH);
    }
  }
  else
  {
    /// @remark LED eteinte si pas de reseau (cmd)
    digitalWrite(LED_BUILTIN,LOW);
    digitalWrite(PIN_LED1,LOW);
  }

  #ifdef ENABLE_WDG
    wdt_reset();
  #endif
}

void reset_time(void)
{
  g_total_s=0;
  Eep::writeTotalTimeCtr(g_total_s);
}

void reset_errs(void)
{
  g_errors=0;
  Eep::writeTotalErrCtr(g_errors);
}

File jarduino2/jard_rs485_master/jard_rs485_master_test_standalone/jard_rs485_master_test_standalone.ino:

#include "pins.h"

#include <FastLED.h>

#define NUM_LEDS  (16)
static CRGB _leds[NUM_LEDS];  ///< Tableau des LEDs

#include <Wire.h>
#include <RTClib.h>
static DS1307 _rtc;

#define STEP_LEDS   (0)
#define STEP_RTC    (1)
#define STEP_RS485  (2)
#define STEP_BUTTON (3)
#define STEP_12V    (4)
#define STEP_33V    (5)
#define STEP_WIFI   (6)

void test_set_led(int inx,int r=0,int g=255,int b=0)
{
  if (inx<NUM_LEDS)
  {
    _leds[inx]=CRGB(r,g,b);
    FastLED.setBrightness(100);
    FastLED.show();
  }
}

void go_in_error(int stp)
{
  test_set_led(stp,255,0,0);
  while(1)
  {
    yield();
    delay(10);
  }
}


void test_leds_rgb(void)
{
  Serial.println("Test LEDs RGB...");
  digitalWrite(PIN_PWR_LEDS,HIGH);
  delay(1000);

  digitalWrite(PIN_PWR_LEDS,LOW);
  for (int i=0;i<NUM_LEDS;i++)
  {
    for (int j=0;j<NUM_LEDS;j++)
    {
      if (i==j)
        _leds[j]=CRGB(127,0,0);
      else
        _leds[j]=CRGB(0,0,0);
    }

    FastLED.setBrightness(255);
    FastLED.show();
    delay(250);    
  }

  for (int j=0;j<NUM_LEDS;j++)
    _leds[j]=CRGB(0,0,0);

  FastLED.setBrightness(10);
  FastLED.show();

  test_set_led(STEP_LEDS,0,255,0);
}

void test_rtc(void)
{
  Serial.println("Test RTC...");
  test_set_led(STEP_RTC,0,0,255); 
  Wire.begin();
  _rtc.begin();

  #ifdef INIT_TIME
    _rtc.adjust(DateTime(__DATE__, __TIME__));
  #endif
  
   DateTime now = _rtc.now();
   char strDte[30];
   sprintf(strDte,"%02d/%02d/%04d %02d:%02d:%02d",
   now.day(),
   now.month(),
   now.year(),
   now.hour(),
   now.minute(),
   now.second()
   );
   Serial.print("Date: ");
   Serial.println(strDte);

   if (now.year()!=2024)
   {
    Serial.println("Date lue NOK!");
    go_in_error(STEP_RTC);
   }
   test_set_led(STEP_RTC,0,255,0); 
}

void test_send_rs485(void)
{
  Serial.println("Test envoi RS485...");
  test_set_led(STEP_RS485,0,0,255);
  Serial1.begin(9600);
  Serial3.begin(9600);

  Serial.println("Send and receive MOTIF...");
  digitalWrite(PIN_TX_EN,HIGH);
  delay(10);
  while (Serial3.available()>0)
    Serial3.read();  
  Serial1.print("MOTIF");
  delay(100);

  if (Serial3.available()<5)
    go_in_error(STEP_RS485);

  String recv=Serial3.readString();  
  Serial.println(recv);  
  if (recv!="MOTIF")
    go_in_error(STEP_RS485);

  Serial.println("TX Disabled...");
  digitalWrite(PIN_TX_EN,LOW);
  delay(50);

  while (Serial3.available()>0)
    Serial3.read();  
  Serial1.println("DESACTIVE");
  delay(100);
  if (Serial3.available()!=0)
    go_in_error(STEP_RS485);
  
  test_set_led(STEP_RS485,0,255,0);   
}

void test_button(void)
{
  Serial.println("Test Bouton...");
  test_set_led(STEP_BUTTON,0,0,255); 
  if (digitalRead(PIN_TEST_BTN)==LOW)
    go_in_error(STEP_BUTTON);
  
  while (digitalRead(PIN_TEST_BTN)==HIGH)
    delay(100);
  test_set_led(STEP_BUTTON,0,255,0);     
}

void test_pwr_12V(void)
{
  Serial.println("Test POWER 12V...");
  for (int i=0;i<3;i++)
  {
    test_set_led(STEP_12V,0,0,255);
    digitalWrite(PIN_PWR_ON,HIGH);
    delay(2000);
    test_set_led(STEP_12V,0,0,0);
    digitalWrite(PIN_PWR_ON,LOW);
    delay(2000);
  }
  test_set_led(STEP_12V,0,255,0);
}

void test_pwr_33V(void)
{
  Serial.println("Test POWER 3.3V...");
  for (int i=0;i<3;i++)
  {    
    test_set_led(STEP_33V,0,0,255);
    digitalWrite(PIN_PWR_WIFI,LOW);
    delay(2000);
    test_set_led(STEP_33V,0,0,0);
    digitalWrite(PIN_PWR_WIFI,HIGH);
    delay(2000);
  }
  test_set_led(STEP_33V,0,255,0);
}

void test_wifi_comm(void)
{
  test_set_led(STEP_WIFI,0,0,255);
  Serial.println("Test comm wifi...");
  Serial2.begin(9600);
  digitalWrite(PIN_PWR_WIFI,LOW);
  delay(5000);
  while (Serial2.available()>0)
    Serial2.read();    
  Serial.println("Send ping...");
  Serial2.print("ping\n");
  delay(1000);
  if (Serial2.available()<5)
    go_in_error(STEP_WIFI);
  
  String recv=Serial2.readString();
  Serial.print("Receive: ");
  Serial.println(recv);
  if (memcmp(recv.c_str(),"pong",4)!=0)
    go_in_error(STEP_WIFI);

  digitalWrite(PIN_PWR_WIFI,HIGH);
  test_set_led(STEP_WIFI,0,255,0);
}

void setup() 
{
  pinMode(PIN_TX_EN,OUTPUT);
  digitalWrite(PIN_TX_EN,LOW);
  pinMode(PIN_TEST_BTN,INPUT_PULLUP);
  
  pinMode(PIN_PWR_ON,OUTPUT);
  digitalWrite(PIN_PWR_ON,LOW);  
  
  pinMode(LED_BUILTIN,OUTPUT);
  digitalWrite(LED_BUILTIN,LOW);
  
  pinMode(PIN_DATA_LEDS,OUTPUT);
  digitalWrite(PIN_DATA_LEDS,LOW);

  pinMode(PIN_PWR_LEDS,OUTPUT);
  digitalWrite(PIN_PWR_LEDS,HIGH);

  pinMode(PIN_PWR_WIFI,OUTPUT);
  digitalWrite(PIN_PWR_WIFI,HIGH);
  
  pinMode(PIN_SD_CS,OUTPUT);
  digitalWrite(PIN_SD_CS,LOW);
  /*pinMode(11,INPUT);
  pinMode(12,INPUT);
  pinMode(13,INPUT);*/

  FastLED.addLeds<NEOPIXEL, PIN_DATA_LEDS>(_leds, NUM_LEDS);
  for (int j=0;j<NUM_LEDS;j++)
    _leds[j]=CRGB(0,0,0);    

  delay(100);
  Serial.begin(9600);  
  Serial.println("Boot Tst Std");
  
  test_leds_rgb();  
  test_rtc();
  test_send_rs485();
  test_button();
  test_pwr_12V();  
  test_pwr_33V();
  test_wifi_comm();

  Serial.println("_________");
  Serial.println("TEST OK !");
  delay(2000);
  for (int j=0;j<NUM_LEDS;j++)
    _leds[j]=CRGB(0,0,0);    
  FastLED.show();
} 


void loop() 
{
}

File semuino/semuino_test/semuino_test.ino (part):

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#define PIN_CMD_P3          (11)  ///< Commande LEDs de puissance 3

#define PIN_TEMP            (12)  ///< Capteur de température DHT
#define PIN_HUM1            (A0)  ///< Entree analogique capteur humidité bas
#define PIN_HUM2            (A1)  ///< Entree analogique capteur humidité haut
#define PIN_HUM3            (A2)  ///< Entree analogique capteur humidité dessus du meuble


#define COL_GROWING         CRGB(127,0,32)      ///< Couleur de croissance
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  digitalWrite(PIN_TEMP, LOW);

  pinMode(PIN_SELECT_BTN, INPUT_PULLUP);
  pinMode(PIN_HUM1, INPUT);
  pinMode(PIN_HUM2, INPUT);
  pinMode(PIN_HUM3, INPUT);

  pinMode(LED_BUILTIN, OUTPUT);
  digitalWrite(LED_BUILTIN, HIGH);
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{
  char tmp[15];
  
  int hum = analogRead(PIN_HUM1);  
  Serial.print("H1:");
  sprintf(tmp,"%d",hum);
  Serial.println(tmp);

  hum = analogRead(PIN_HUM2);
  Serial.print("H2:");
  sprintf(tmp,"%d",hum);
  Serial.println(tmp);

  hum = analogRead(PIN_HUM3);
  Serial.print("H3:");
  sprintf(tmp,"%d",hum);
  Serial.println(tmp);
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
